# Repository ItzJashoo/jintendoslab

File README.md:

A project to make a 2DS like game console, first PCB project ever, going to have a battery and a Raspberry Pi 2 W.
Will have a dPad, XYAB, Start Select, Power, Special, and 4 triggers.
I made this as I don't have any retro consoles and I thought this is a fun way to learn CAD design and PCB design, to make something that I would use and would enjoy. Another reason why is that I saw this project on the starter projects section and I was like, hey, that's a great idea!
It will have a 64GB SD card running RetroPie (trying to use the Pi-Tin version). Linked here: https://github.com/jackw01/pi-tin/releases/download/v1.0/pi_tin_20250316.zip
Note: I did use breakout boards from Adafruit in this project, they can be found on their respective websites.

THE BOM BELOW IS OUTDATED, PRESS THIS LINK WITH THE LATEST VERSION WITH UP TO DATE COSTS AND PART LINKS: https://docs.google.com/spreadsheets/d/1hn2z8ekfqbGUfXvgOQFQ-BLUxkavOTLEDDJ-F8h76a0/edit?gid=0#gid=0

| Item                               | Cost (USD)      |
|------------------------------------|-----------------|
| Battery                            | $12.50          |
| Charging & Booster board           | $19.95          |
| Amp                                | $5.95           |
| Speaker                            | $2.22           |
| Start/Select/Special buttons       | $0.84           |
| Trigger buttons                    | $1.48           |
| Other buttons (XYAB, DPAD)         | $0.80           |
| Raspberry Pi 2W                    | $16.50          |
| 2.8 inch Display with Control board| $29.95          |
| SD Card                            | $4.49           |
| Wires                              | $2.95           |
| Wire strippers                     | $6.95           |
| 82 kohm resistor                   | $0.10           |
| 100 kohm resistor                  | $0.10           |
| PCBWay PCB                         | $0.00 (coupon)  |
| Screws, nuts, washers set          | $9.99           |
| **Total (tax&shipping component)** | **$124.586**    |

Additional costs for soldering iron, wick, flux, solder, stand and sponge.
Added up is 161.69, which is below the 168 total grant (150+18 solder) minus the PCB cost (just shipping for 5.68).

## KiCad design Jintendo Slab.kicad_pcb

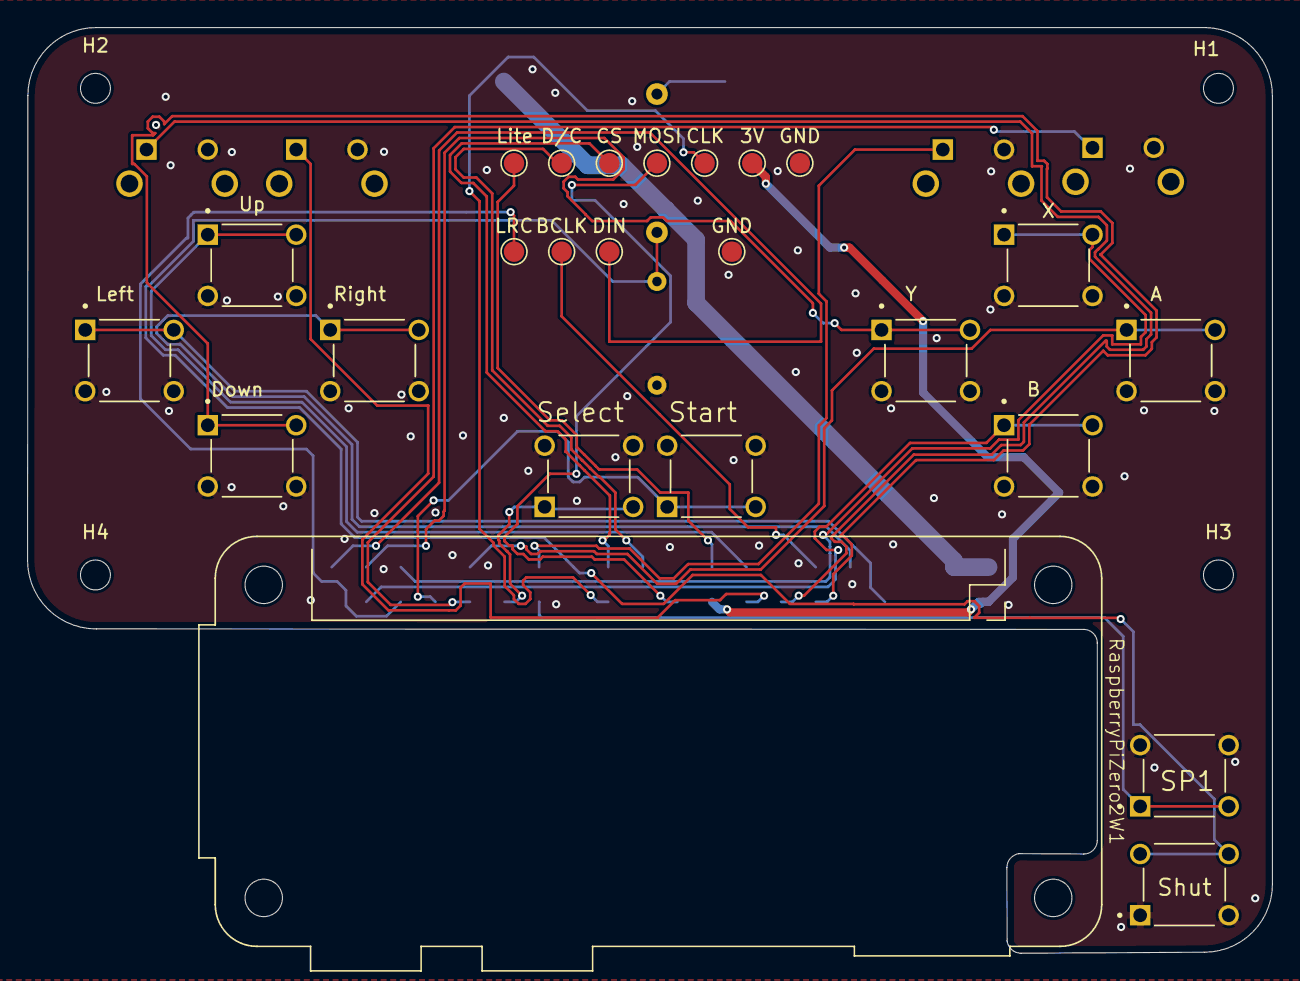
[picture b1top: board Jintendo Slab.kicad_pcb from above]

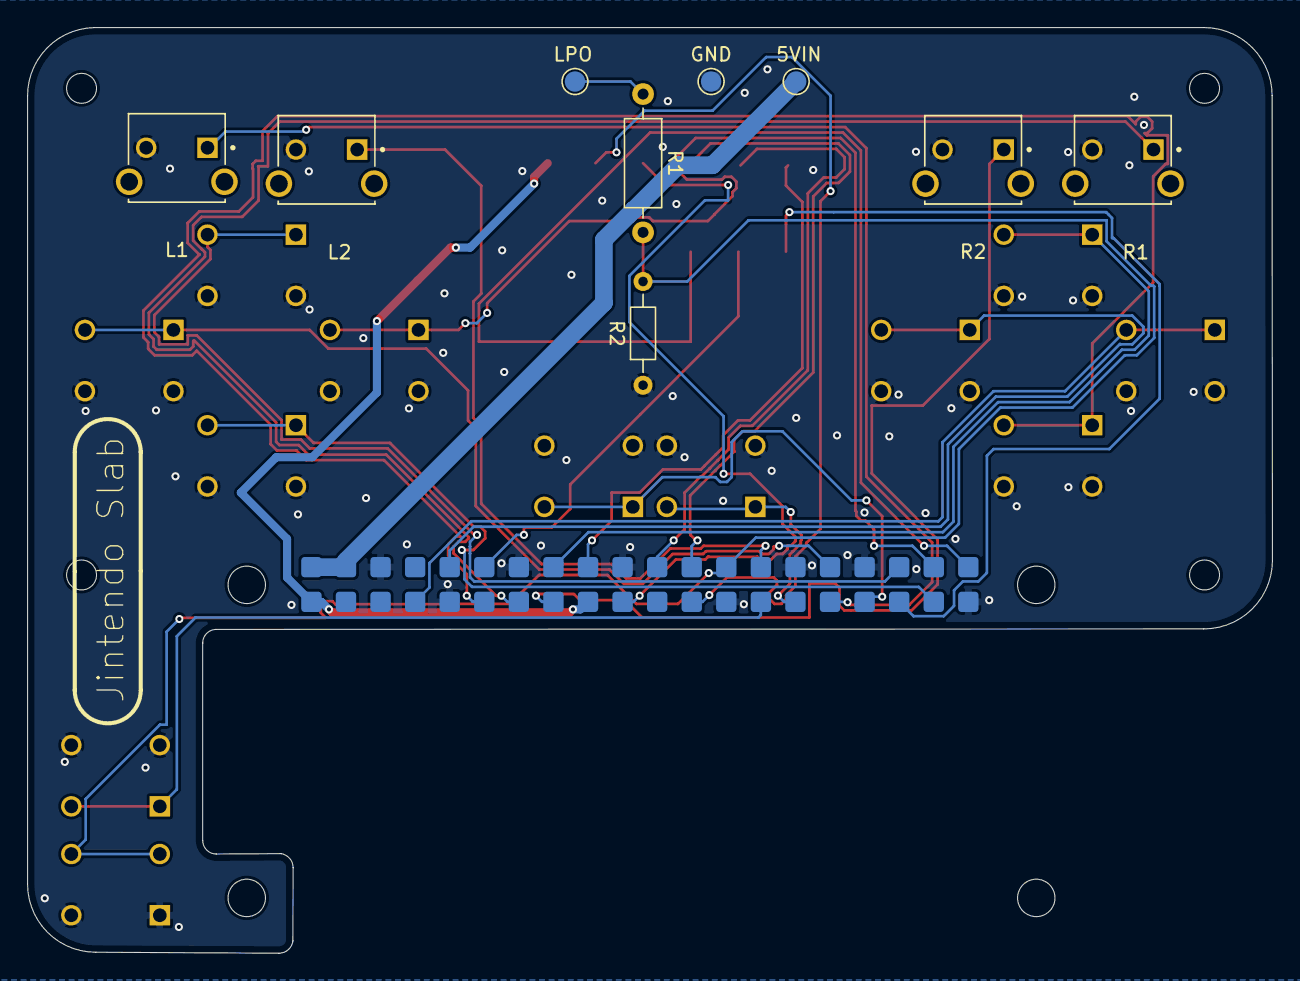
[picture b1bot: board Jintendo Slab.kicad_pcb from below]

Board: 2 copper layers, 91.5 x 68.0 mm, 37 parts (9 on the bottom side), 28 nets.

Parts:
3V: 3V; TestPoint_Pad_D1.5mm
5VIN: 5V Input; TestPoint_Pad_D1.5mm
A: SW_Controls; SW_Control
B: SW_Controls; SW_Control
BCLK: BCLK; TestPoint_Pad_D1.5mm
CLK: CLK; TestPoint_Pad_D1.5mm
CS: CS; TestPoint_Pad_D1.5mm
D/C: D/C; TestPoint_Pad_D1.5mm
DIN: DIN; TestPoint_Pad_D1.5mm
Down: SW_Controls; SW_Control
GND: GND; TestPoint_Pad_D1.5mm
GND#2: GND; TestPoint_Pad_D1.5mm
GND#3: Ground; TestPoint_Pad_D1.5mm
H1, H2, H3, H4: MountingHole; MountingHole_2.2mm_M2
L1, L2: SW_Trigger
LPO: LPO Input; TestPoint_Pad_D1.5mm
LRC: LRC; TestPoint_Pad_D1.5mm
Left: SW_Controls; SW_Control
Lite: Lite; TestPoint_Pad_D1.5mm
MOSI: MOSI; TestPoint_Pad_D1.5mm
R1: 100kOhm; R_Axial_DIN0207_L6.3mm_D2.5mm_P10.16mm_Horizontal
R1#2, R2: SW_Trigger
R2#2: 82 kOhm; R_Axial_DIN0204_L3.6mm_D1.6mm_P7.62mm_Horizontal
RaspberryPiZero2W1: RaspberryPiZero2W
Right: SW_Controls; SW_Control
SP1: SW_Special
Select: SW_Special
Shut: SW_Special
Start: SW_Special
Up: SW_Controls; SW_Control
X: SW_Controls; SW_Control
Y: SW_Controls; SW_Control

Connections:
+3V3: 3V.1, RaspberryPiZero2W1.1 (3V3[1]), RaspberryPiZero2W1.17 (3V3[2])
+5V: 5VIN.1, RaspberryPiZero2W1.2 (5V[1]), RaspberryPiZero2W1.4 (5V[2])
/A: A.1, RaspberryPiZero2W1.32 (GPIO12)
/B: B.1, RaspberryPiZero2W1.37 (GPIO26)
/BL: Lite.1, RaspberryPiZero2W1.18 (GEN5/GPIO24)
/CS0: CS.1, RaspberryPiZero2W1.24 (~CE0/GPIO8)
/DOWN: Down.1, RaspberryPiZero2W1.11 (GPIO17/GEN0)
/D/C: D/C.1, RaspberryPiZero2W1.22 (GEN/6GPIO25)
/I2S_BCLK: BCLK.1, RaspberryPiZero2W1.12 (GPIO18)
/I2S_DIN: DIN.1, RaspberryPiZero2W1.40 (GPIO21)
/I2S_LRCLK: LRC.1, RaspberryPiZero2W1.35 (GPIO19)
/L1: L1.1, RaspberryPiZero2W1.31 (GPIO6)
/L2: L2.1, RaspberryPiZero2W1.28 (ID_SC)
/LEFT: Left.1, RaspberryPiZero2W1.7 (GPIO4/GPCKL0)
/MOSI: MOSI.1, RaspberryPiZero2W1.19 (GPIO10/MOSI)
/R1: R1#2.1, RaspberryPiZero2W1.13 (GPIO27/GEN2)
/R2: R2.1, RaspberryPiZero2W1.15 (GPIO22/GEN3)
/RIGHT: RaspberryPiZero2W1.10 (RXD0/GPIO15), Right.1
/SCLK: CLK.1, RaspberryPiZero2W1.23 (GPIO11/SCLK)
/SELECT: RaspberryPiZero2W1.29 (GPIO5), Select.1
/SHUTDOWN_PI: R1.2, R2#2.2, RaspberryPiZero2W1.26 (~CE1/~GPIO7), Shut.2
/SPECIAL1: RaspberryPiZero2W1.27 (ID_SD), SP1.1
/START: RaspberryPiZero2W1.33 (GPIO13), Start.1
/UP: RaspberryPiZero2W1.16 (GEN4/GPIO23), Up.1
/X: RaspberryPiZero2W1.36 (GPIO16), X.1
/Y: RaspberryPiZero2W1.38 (GPIO20), Y.1
GND: A.2, B.2, Down.2, GND.1, GND#2.1, GND#3.1, L1.2, L2.2, Left.2, R1#2.2, R2.2, R2#2.1, RaspberryPiZero2W1.6 (GND[8]), RaspberryPiZero2W1.9 (GND[1]), RaspberryPiZero2W1.14 (GND[4]), RaspberryPiZero2W1.20 (GND[5]), RaspberryPiZero2W1.25 (GND[2]), RaspberryPiZero2W1.30 (GND[6]), RaspberryPiZero2W1.34 (GND[7]), RaspberryPiZero2W1.39 (GND[3]), Right.2, SP1.2, Select.2, Shut.1, Start.2, Up.2, X.2, Y.2
unnamed: LPO.1, R1.1

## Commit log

2025-06-01 Update JOURNAL.md
    update to today
2025-06-04 Update JOURNAL.md
    Late update mb
2025-06-11 Add files via upload
    updated models to fit new power board
2025-06-11 V2 of costs
2025-06-11 The SW_Special buttons were wired wrong
    I thought it was
    1 2
    1 2
    not
    1 1
    2 2
2025-06-11 Fixed spacing to better suit the DFM checks
    Moved some vias further away from traces and stuff, fixed silkscreen overlaps, etc
2025-06-11 Separated top and bottom and other
    Made top and bottom into two different STEP files, and widened holes from M2.5 to M3 as M3x25mm screws are way cheaper.
2025-06-13 Made screw holes bigger AGAIN
    So I checked Home Depot and I saw that they had these #6-32 x 1 Inch screws WITH NUTS for ONLY 1.47!! Which is basically 5 times cheaper than the last commit where I made the holes to M3. So uhh yay!
2025-06-15 Made speaker and button cutouts bigger
    To fit parts better
